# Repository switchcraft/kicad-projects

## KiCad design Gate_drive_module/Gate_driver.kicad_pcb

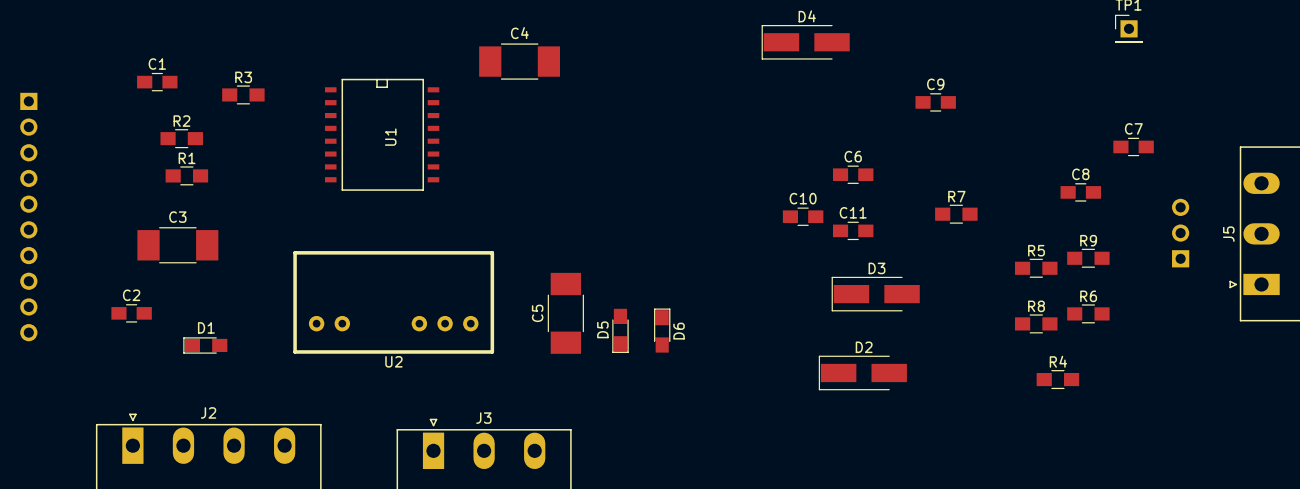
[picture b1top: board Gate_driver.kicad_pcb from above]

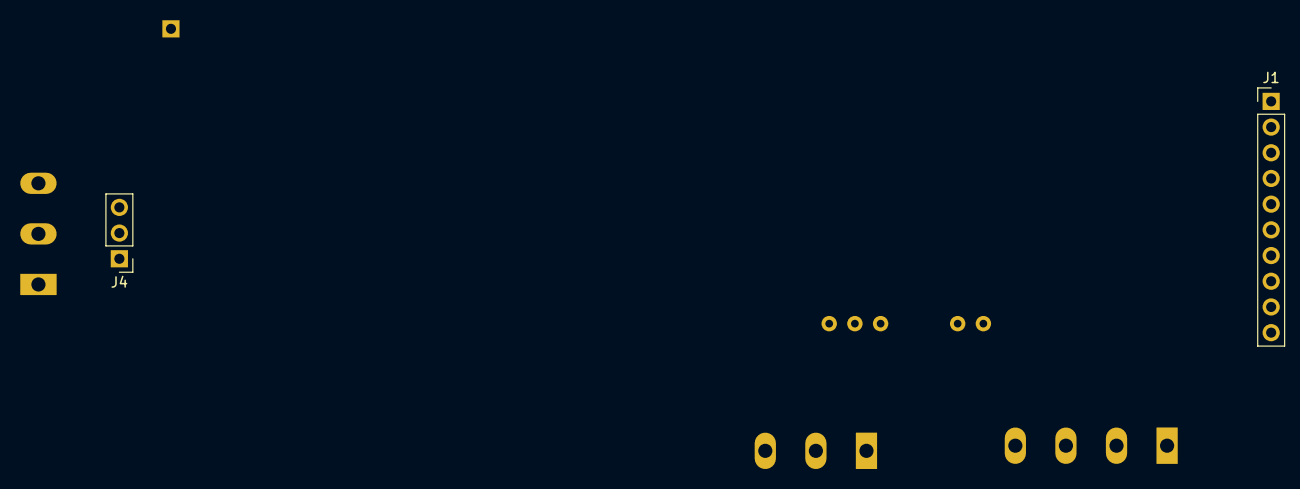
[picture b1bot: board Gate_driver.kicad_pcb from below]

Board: 2 copper layers, 34 parts (2 on the bottom side), 20 nets, no tracks yet.

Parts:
C1, C7, C8, C9: 10u; C_0805_HandSoldering
C2, C10, C11: 100n; C_0805_HandSoldering
C3, C4, C5: 100u; C_1812_HandSoldering
C6: 100p; C_0805_HandSoldering
D1: RED PWR LED; LED_0805_HandSoldering
D2, D3: D; D_SMA_Handsoldering
D4: ES1F; D_SMA_Handsoldering
D5, D6: GREEN PWR LED; LED_0805_HandSoldering
J1: CONN_01X10; Pin_Header_Straight_1x10_Pitch2.54mm
J2: CONN_01X04; MSTBA_25_4p_G_508-1757268
J3, J5: CONN_01X03; MSTBA_25_3p_G_508-1757488
J4: CONN_01X03; Pin_Header_Straight_1x03_Pitch2.54mm
R1, R2, R3, R8, R9: 10k; R_0805_HandSoldering
R4, R5, R6: 100R; R_0805_HandSoldering
R7: 100k; R_0805_HandSoldering
TP1: TEST; Pin_Header_Straight_1x01_Pitch2.54mm
U1: HCPL-316J; SO-16-W
U2: Mornsun_QA01C; QA01C

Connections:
+15V: C3.1, J1.10, J2.4, U2.1
GND: C1.2, C2.2, C3.2, D1.1, J1.1, J2.1, U1.4, U1.8, U2.2
GND_ISO: C4.2, C5.1, C6.2, C8.2, C9.1, C10.2, C11.1, D5.1, J3.2, J4.3, J5.3, R7.1, R9.1, U1.16, U2.6
unnamed: C6.1, R6.2, U1.14
unnamed: D1.2, R2.2
unnamed: D2.1, R4.2
unnamed: D2.2, D3.1, U1.11
unnamed: D3.2, R5.2
unnamed: D4.1, J4.1, J5.1
unnamed: D4.2, R6.1, TP1.1
unnamed: D5.2, R8.2
unnamed: D6.2, R9.2
unnamed: J1.4, R3.2, U1.6
unnamed: J1.5, R1.2, U1.5
unnamed: J1.6, U1.2
unnamed: J1.7, U1.1
unnamed: J4.2, J5.2, R4.1, R5.1, R7.2
VCC: C1.1, C2.1, J1.8, J2.2, R1.1, R2.1, R3.1, U1.3
VCC_ISO: C4.1, C7.1, C8.1, C10.1, J3.3, R8.1, U1.12, U1.13, U2.7
VEE_ISO: C5.2, C7.2, C9.2, C11.2, D6.1, J3.1, U1.9, U1.10, U2.5

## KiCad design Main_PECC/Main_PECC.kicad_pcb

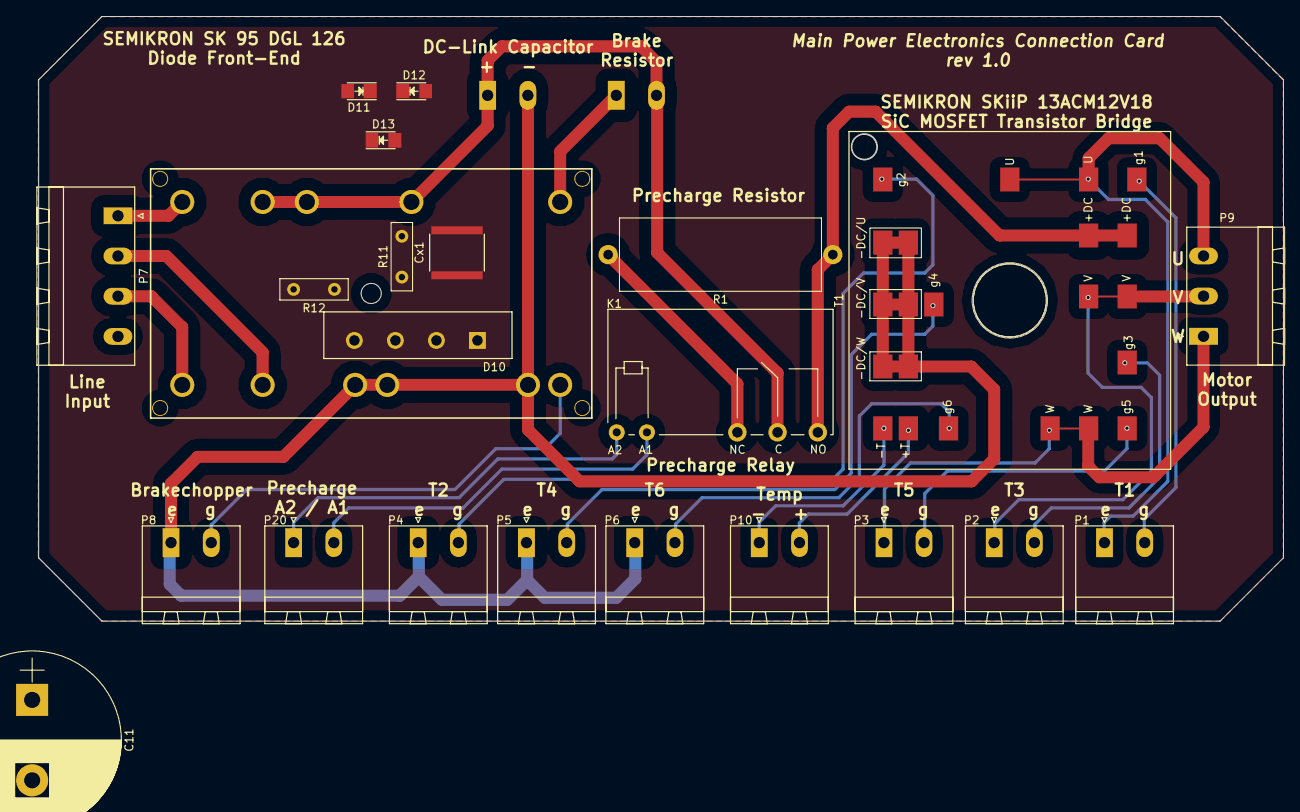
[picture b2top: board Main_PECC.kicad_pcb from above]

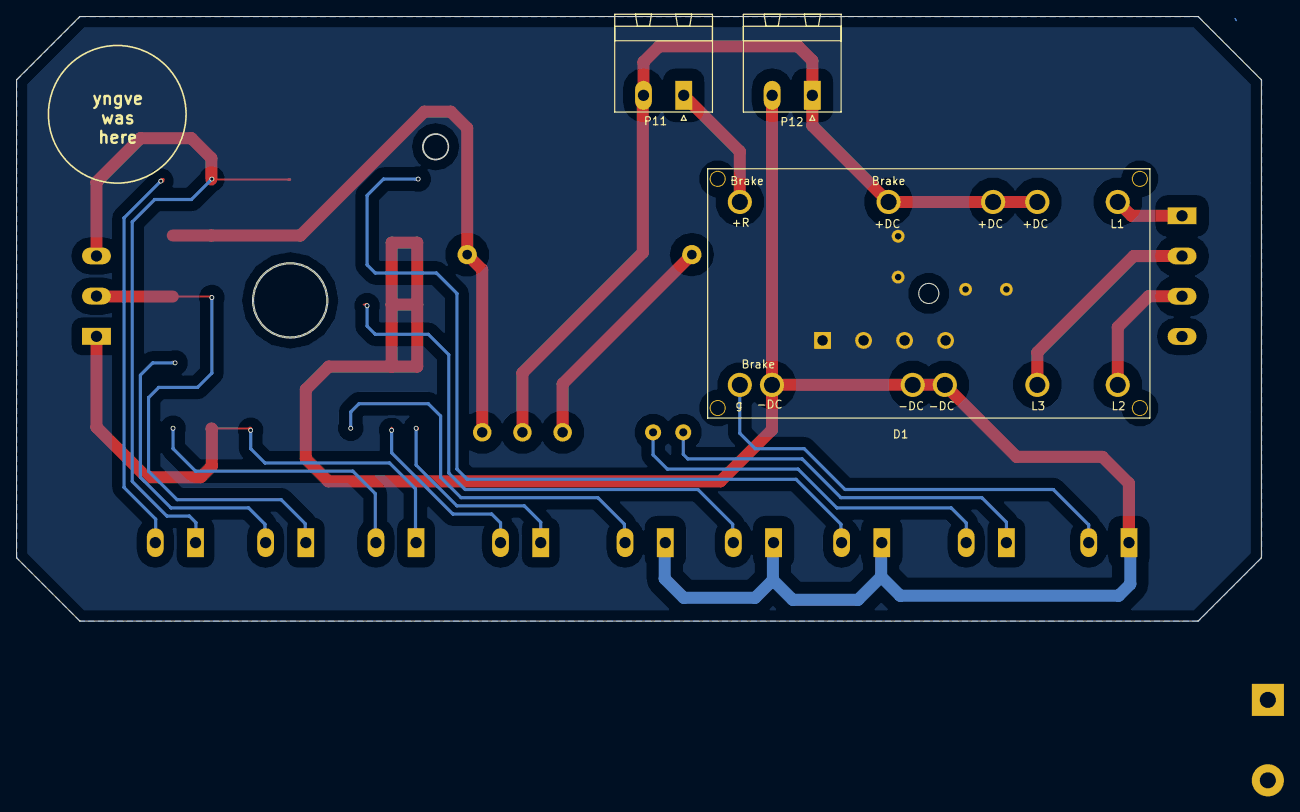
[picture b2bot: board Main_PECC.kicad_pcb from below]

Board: 2 copper layers, 154.8 x 75.2 mm, 25 parts (3 on the bottom side), 28 nets.

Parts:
C11: 100uF/25V; CP_Radial_D22.0mm_P10.00mm_SnapIn
Cx1: 472K/400V; C_2225
D1: SK_95_DGL_126
D10: D_Bridge_+-AA; Diode_Bridge_18.5x5.5
D11, D12, D13: LED; LED_1206
K1: RELAY_1RT; Relay_SPDT_SingleRow_Laying_FinderType34Point51
P1, P2, P3, P4, P5, P6, P8, P10, P11, P12, P20: CONN_01X02; PhoenixContact_MSTBA-G_02x5.00mm_Angled
P7: CONN_01X04; PhoenixContact_MSTBA-G_04x5.00mm_Angled
P9: CONN_01X03; PhoenixContact_MSTBA-G_03x5.00mm_Angled
R1: R; R_Axial_Power_L25.0mm_W9.0mm_P27.94mm
R11: 470k 1W; R_Box_L8.4mm_W2.5mm_P5.08mm
R12: 470/1W; R_Box_L8.4mm_W2.5mm_P5.08mm
T1: SemikronSKiiP_13ACM12V18; SKiiP_13ACM12V18_3d_ver3

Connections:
A1: K1.A1, P20.2
A2: K1.A2, P20.1
L1: Cx1.2, D1.1, P7.1, R11.2
L2: D1.15, P7.3, R12.2
unnamed: C11.1, D10.1, D11.2
unnamed: C11.2, D10.2, D13.1
unnamed: Cx1.1, D10.3, R11.1
unnamed: D1.4, D1.5, D1.9, K1.11, P11.2, P12.1
unnamed: D1.14, P11.1
unnamed: D1.18, P7.2
unnamed: D1.21, D1.22, D1.27, P4.1, P5.1, P6.1, P8.1, P12.2, T1.9, T1.10, T1.11, T1.12, T1.13, T1.14
unnamed: D1.28, P8.2
unnamed: D10.4, R12.1
unnamed: D11.1, D12.2
unnamed: D12.1, D13.2
unnamed: K1.12, R1.2
unnamed: K1.14, R1.1, T1.7, T1.8
unnamed: P1.1, P9.3, T1.15, T1.16
unnamed: P1.2, T1.1
unnamed: P2.1, P9.2, T1.17, T1.18
unnamed: P2.2, T1.3
unnamed: P3.1, P9.1, T1.19, T1.20
unnamed: P3.2, T1.5
unnamed: P4.2, T1.2
unnamed: P5.2, T1.4
unnamed: P6.2, T1.6
unnamed: P10.1, T1.22
unnamed: P10.2, T1.21
